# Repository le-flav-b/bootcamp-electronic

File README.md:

## Bill Of Materials

| Manufacture Part Number | Manufacturer               | Package      | Description                      | Quantity |
| ----------------------- | -------------------------- | ------------ | -------------------------------- | -------- |
| ATMEGA328P-AU           | MICROCHIP                  | TQFP-32(7x7) | AVR Microcontroller - ATmega328p | 1        |
| X322516MLB4SI           | YXC Crystal Oscillators    | SMD3225-4P   | Crystal Oscillator - 16MHz 9pF   | 1        |
| B3U-1000P               | OMRON                      | SMD,3x2.5mm  | Round Button - 2.5mm 12V         | 1        |
| TZ-P2-0603YGTCS1-0.6T   | TUOZHAN                    | 0603         | Indication LED - Green 1.9V~2.4V | 1        |
| XL-1608SURC-06          | XINGLIGHT                  | 0603         | Indication LED - Red 2.3V        | 1        |
| CL10A105KB8NNNC         | Samsung Electro-Mechanics  | 0603         | Ceramic Capacitor - 1uF 50V      | 1        |
| CC0603KRX7R9BB104       | YAGEO                      | 0603         | Ceramic Capacitor - 100nF 50V    | 3        |
| CL10C120JB8NNNC         | Samsung Electro-Mechanics  | 0603         | Ceramic Capacitor - 12pF 50V     | 2        |
| RC0603FR-0710KL         | YAGEO                      | 0603         | Chip Resistor - 10kΩ 75V         | 2        |
| 0603WAF3300T5E          | UNI-ROYAL                  | 0603         | Chip Resistor - 330Ω 75V         | 1        |

<br>

## Pinout Description

<pre>
      _______________
     |○             ◻|
     |○             ○|
     |○             ○|
     |○             ○|
     |○             ○|
     |○             ○| ← J1
J2 → |○             ○|
     |○             ○|
     |○             ○|
     |○ ◻ ○ ○ ○ ○ ○ ○|
     |○|‾‾‾‾↑‾‾‾‾‾‾|○|
     |◻|    J3     |○|
      ‾             ‾
</pre>

|    |  1            |  2        |  3            |  4       |  5       |  6       |  7       |  8       |  9        |  10           |  11        |  12       |
| -- | :-----------: | :-------: | :-----------: | :------: | :------: | :------: | :------: | :------: | :-------: | :-----------: | :--------: | :-------: |
| J1 | PB1 (D9)      | PB0 (D8)  | PD7 (D7)      | PD6 (D6) | PD5 (D5) | PD4 (D4) | PD3 (D3) | PD2 (D2) | GND       | PC6 (RST/DTR) | PD0 (RXI)  | PD1 (TXO) |
| J2 | VCC/RAW       | GND       | PC6 (RST/DTR) | VCC/RAW  | PC3 (A3) | PC2 (A2) | PC1 (A1) | PC0 (A0) | PB5 (SCK) | PB4 (MISO)    | PB3 (MOSI) | PB2 (D10) |
| J3 | PC6 (RST/DTR) | PD1 (TXO) | PD0 (RXI)     | VCC/RAW  | GND      | GND      |          |          |           |               |            |           |

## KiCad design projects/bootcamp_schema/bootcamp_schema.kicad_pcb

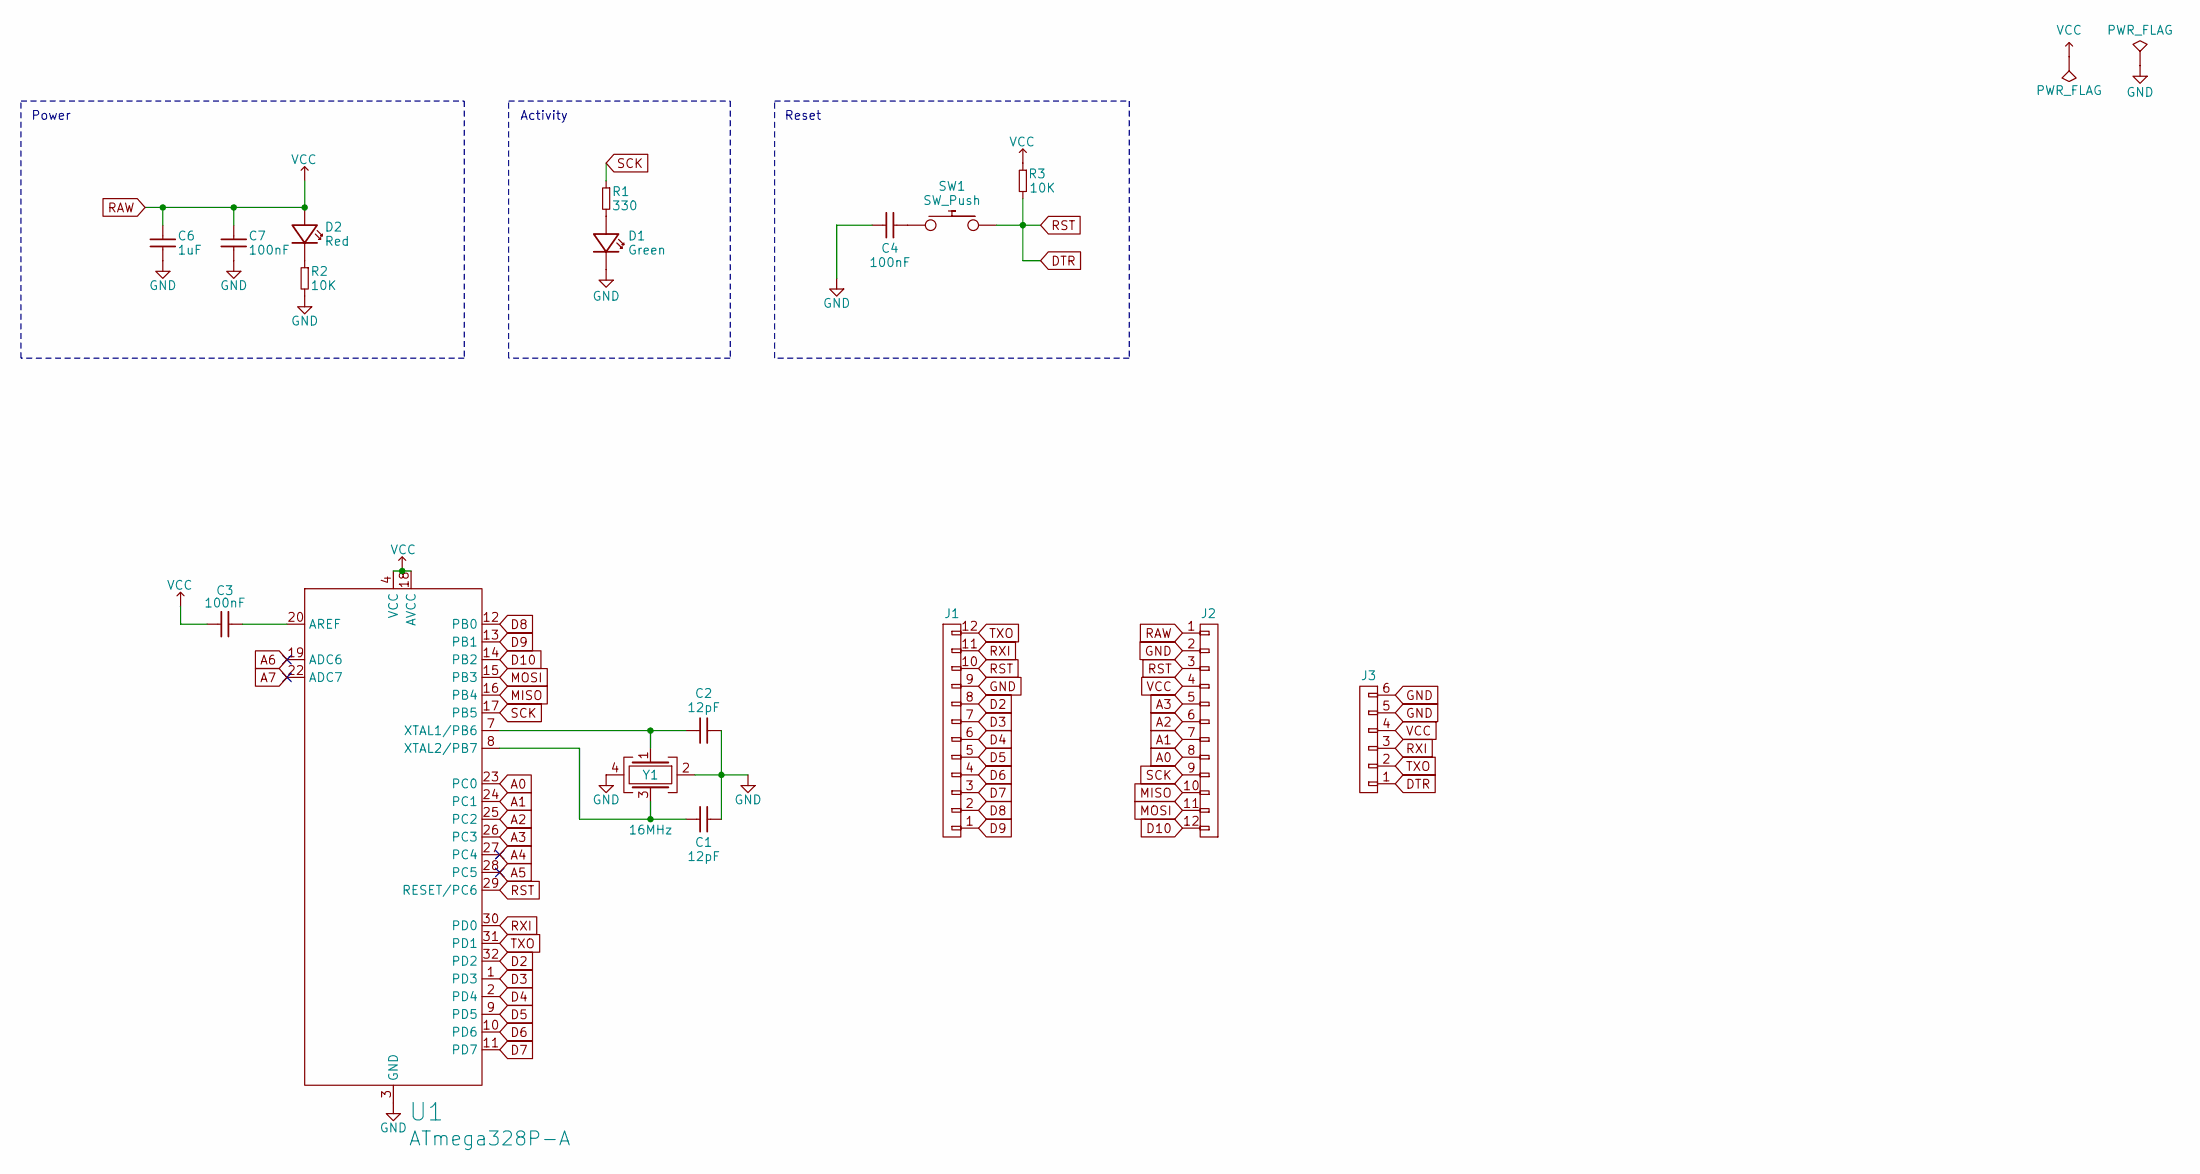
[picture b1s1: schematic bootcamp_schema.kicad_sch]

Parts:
C1, C2: 12pF; capacitor_generic_smt
C3, C4, C7: 100nF; capacitor_generic_smt
C6: 1uF; capacitor_generic_smt
D1: Green; led_green_smt
D2: Red; led_red_smt
J1, J2: connector_j12_tht
J3: connector_j6_tht
R1: 330; resistor_330_smt
R2, R3: 10K; resistor_10k_smt
SW1: SW_Push; button_push_smt
U1: ATmega328P-A; chip_atmega328p_smt
Y1: 16MHz; oscillator_16MHz_smt

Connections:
A0: J2.8, U1.23 (PC0)
A1: J2.7, U1.24 (PC1)
A2: J2.6, U1.25 (PC2)
A3: J2.5, U1.26 (PC3)
A4: U1.27 (PC4)
A5: U1.28 (PC5)
A6: U1.19 (ADC6)
A7: U1.22 (ADC7)
D2: J1.8, U1.32 (PD2)
D3: J1.7, U1.1 (PD3)
D4: J1.6, U1.2 (PD4)
D5: J1.5, U1.9 (PD5)
D6: J1.4, U1.10 (PD6)
D7: J1.3, U1.11 (PD7)
D8: J1.2, U1.12 (PB0)
D9: J1.1, U1.13 (PB1)
D10: J2.12, U1.14 (PB2)
DTR: J1.10, J2.3, J3.1, R3.2, SW1.2, U1.29 (RESET/PC6)
MISO: J2.10, U1.16 (PB4)
MOSI: J2.11, U1.15 (PB3)
unnamed: C4.2, SW1.1
unnamed: D1.1, R1.2
unnamed: D2.2, R2.1
unnamed: C3.2, U1.20 (AREF)
unnamed: C2.1, U1.7 (XTAL1/PB6), Y1.1
unnamed: C1.1, U1.8 (XTAL2/PB7), Y1.3
RXI: J1.11, J3.3, U1.30 (PD0)
SCK: J2.9, R1.1, U1.17 (PB5)
TXO: J1.12, J3.2, U1.31 (PD1)

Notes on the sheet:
Reset
Power
Activity

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
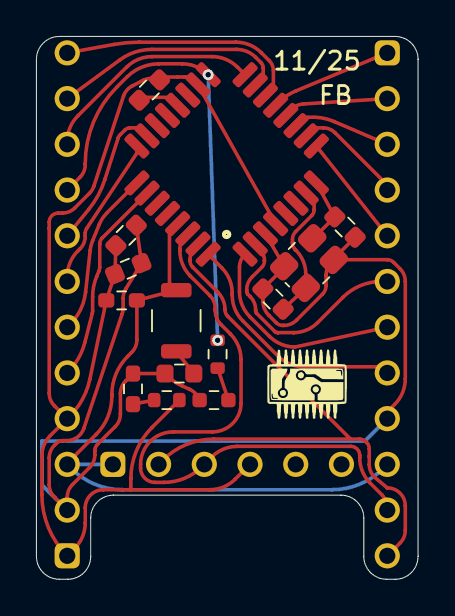
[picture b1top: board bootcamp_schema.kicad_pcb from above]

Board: 2 copper layers, 21.2 x 30.2 mm, 18 parts (0 on the bottom side), 27 nets.

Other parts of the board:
11/25: LOGO; logo

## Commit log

2025-11-23 PCB finished
2025-11-23 added readme
2025-11-23 improved readme BOM table
2025-11-23 added pinout description to readme
2025-11-23 corrected BOM in readme
2025-11-24 added lib tables
2025-11-24 updated lib tables with relative path
2025-11-24 added chip pin names in pinout table
2025-11-24 fix formatting in schema of readme
